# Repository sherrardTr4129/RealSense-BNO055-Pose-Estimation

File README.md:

# RealSense-BNO055-Pose-Estimation
This repository contains required software to construct a Pose of a vision target by fusing its x,y,z coordinates from the Intel RealSense depth camera, with its quaternion orientation from the BNO055 sensor.

## Demo Video
Have a look at the youtube video below to see the system in action!

## System Description
As mentioned, this system seeks to capture the position (x,y,z coordinates) of a vision target using an Intel RealSense depth camera, while capturing it's orientation as a quaternion using a BNO055 sensor. These two data streams are combined into a 6-DOF pose using an approximate time synchornization technique. This system has a multitude of uses in the problem domain of human-robot interaction. Some of these applications include the generation of end-effector goal poses for a "mimic-me" teleoperation robot arm, or potentially the generation of entire arm trajectories for a robot arm to follow. Please have a look at the high-level system block diagram below.

### Intel RealSense Position Capture
The Intel RealSense position capture sub-system attempts to locate the vision target in a given RGB frame, and then attempts to extract the vision target's approximate depth and X,Y coordinates in the camera's coordinate frame. From here, these values are scaled and shifted accordingly and re-published to the rest of the system as a PointStamped message. Have a look at this sub-system's block diagram and a physical representation of the system components below. 

### BNO055 Orientation Capture
The BNO055 orientation capture sub-system attempts to determine the orientation of the vision target as a quaternion, and then wirelessly transmit said quaternion back to a base-station MCU. The base-station MCU then sends the quaternion to a ROS node running on a local computer via a serial interface. This ROS node processes the quaternion components and publishes it as a quaternionStamped message to the rest of the system. All designs (mechanical, electrical and firmware) needed to construct the wirless orientation capture sub-system can be found [here](https://github.com/sherrardTr4129/Kinect-BNO055-Pose-Estimation/tree/main/orientation_capture_subsystem_hardware_and_firmware). The overall sub-system block diagram, functional flowchart diagram, as well as a visual representation of the system can be seen in the figures below.

## System Dependencies
The various dependencies of the system can be seen in the following sub-sections.

### Intel RealSense Dependencies
To run the Intel RealSense interfacing software generated in this project, make sure you have installed the [RealSense SDK 2](https://dev.intelrealsense.com/docs/compiling-librealsense-for-linux-ubuntu-guide) with python bindings.

### MCU Serial Interface Dependencies
The wirelss orientation data reciever MCU serial ROS driver depends on the pyserial library for serial connectiviy. This library can be installed by running the following command in a terminal:

```bash
sudo apt install python-serial
```

### Arduino Firmware Dependencies
Both the transmitter module and reciever module depend on the NRF24 library that can be obtained through the arduino IDE package manager. The transmitter module firmware also depends on the BNO055 sensor adafruit library and the adafruit unified sensor library (both can be obtained in the arduino IDE package manager. 

## Usage
This repository contains three distinct ROS packages that are described in more detail below. 

To launch both the Intel RealSense depth camera position capture node, BNO055 serial ROS driver, and sensor data stream fusion node, run the following in a terminal:
```bash
roslaunch kinect_bno_fusion kinect_bno_fusion_bringup.launch
```

Once these nodes are up and running successfully, you can launch the gazebo visualization tool by running the following in a terminal:
```bash
roslaunch gazebo_pose_example kinect_set_pose_demo.launch
```
This will launch a Gazebo instance, in which a cube will be instantiated that will have it's Pose set by the Pose generated from the sensor data fusion node that was launched in the last step.

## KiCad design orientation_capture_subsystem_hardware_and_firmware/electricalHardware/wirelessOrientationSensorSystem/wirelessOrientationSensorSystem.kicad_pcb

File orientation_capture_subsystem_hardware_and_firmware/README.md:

# Orientation Capture Sub-System Designs (Electrical and Mechanical) and Firmware
This directory contains the hardware designs (mechanical and electrical) and firmware needed to construct the wireless orientation capture system used for more robust motion capture.

# Overall System Specifications
The table below outlines some basic specifications for the overall orientation capture sub-system:

|                       Specification                       |                              Value                              |
|:---------------------------------------------------------:|:---------------------------------------------------------------:|
| Transmitter Range                                         | At least 5m (probably much more even at the NRF24_PA_LOW value) |
| Transmitter Sub-System Current Consumption (steady state) | ~50mA                                                           |
| Battery Life (Assuming 1Ah cell)                          | ~20 hours                                                       |
| Transmitter Input Voltage (4 AA battery cell recommended) | 5V - 6V                                                         |
| Overall System Data Frame Rate                            | ~30 FPS                                                         |

# Electrical Hardware Designs
For this project, a PCB was designed containing all required hardware to read data packets from the BNO055 sensor and transmit them wirelessly to a basestation, where they can be read in by the aforementioned ROS driver. The kiCAD project containng the schematic and board layout files can be found in the electricalHardware/wirelessOrientationSensorSystem directory in this repository. Please see below for a wiring diagram for both the base-station and wireless transmitter board and well as real pictures of each device. 

## Sensor Data Transmitter

Please note that this diagram depicts the wireless data tranmission module in its operational state. More connections are required to flash the firmware to the device. These connections and the firmware flashing process will be outlined later in this readme.

## Sensor Data Reciever 

# Firmware
The firmware flashing process for each of the board assemblies can be seen in each respective sub-section.

## Sensor Data Transmitter Firmware Flashing Procedure
As this board uses a unflashed ATMEGA328P processor, we must first flash the arduino bootloader to the device. The first step in this process is to wire an external arduino uno to the wireless data transmitter board in the configuration seen below. 

From here, upload the arduino as ISP sketch to the arduino uno found under File->Examples->ArduinoISP. Once this successfully uploads to the arduino uno, the bootloader can be flashed. The first step in the flashing process is to change the programmer under Tools->Programmer from "AVRISP mkll" to "Arduino As ISP". From here, click Tools->Burn Bootloader. If the process works as expected, a "bootloader flashed successfully" message will appear in the status window of the IDE

To flash the application level firmware onto the board, first disconnect the arduino uno from the wireless sensor transmitter board. From here, wire up the FTDI USB to TTL Serial converter to the wireless sensor transmitter as shown in the figure below.

From here, open the BNO005_Capture_and_Transmit.ino file in the Arduino IDE. Change the programmer back to "AVRISP mkll" from "Arduino As ISP". Make sure the correct serial port and board type (arduino uno) are selected under the tools menu. From here, click the upload button, and the source should compile and be uploaded to the MCU. 

## Sensor Data Reciever Firmware Flashing Procedure
The process for flashing the firmware for the reciever sub-system is the same as flashing any standard Arduino Uno. Just make sure you have all the NRF24 dependencies installed and compile and upload the firmware. 

# Mechanical Hardware Designs 
The mechanical hardware designs for both the vision target and the base station can be seen in the rendered images below. Note that both the these STL files are available in this repository.

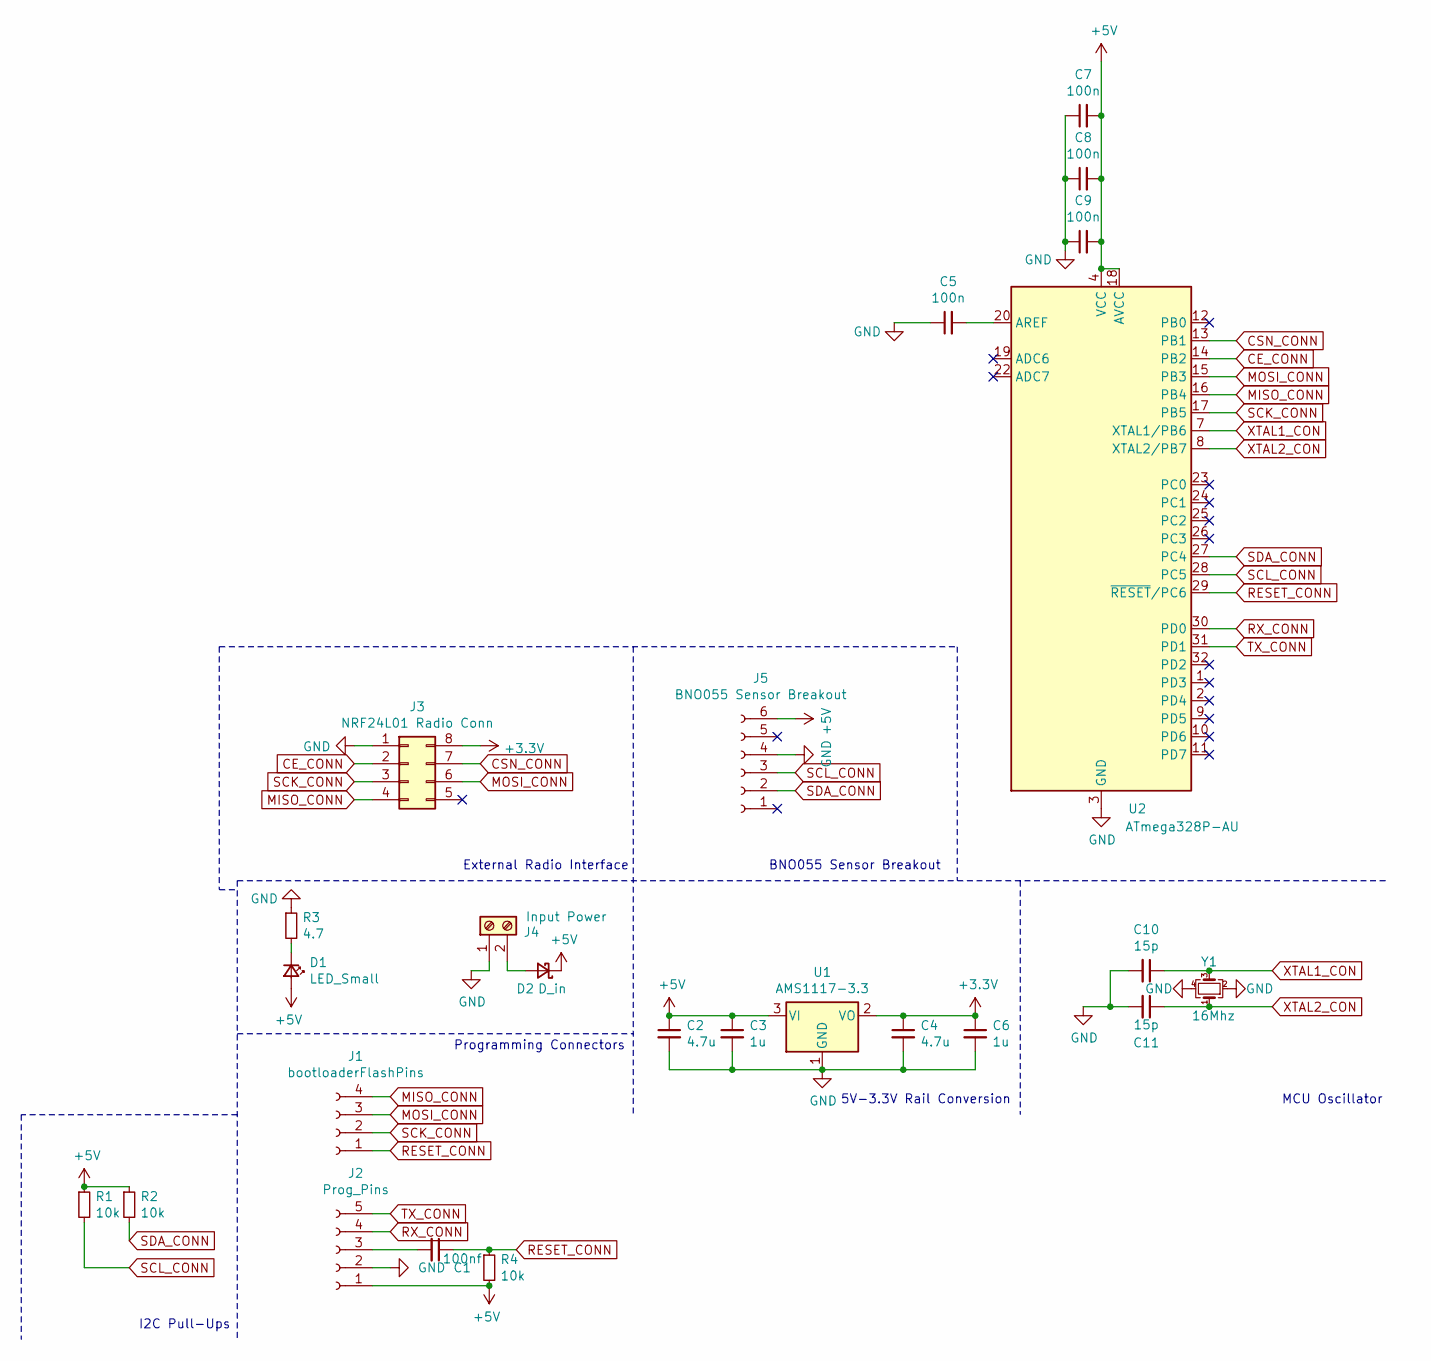
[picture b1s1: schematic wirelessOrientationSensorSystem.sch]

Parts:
C1: 100nf; C_0603_1608Metric; LCSC C14663
C2, C4: 4.7u; C_0805_2012Metric; LCSC C1779
C3, C6: 1u; C_0805_2012Metric; LCSC C28323
C5, C7, C8, C9: 100n; C_0603_1608Metric; LCSC C14663
C10, C11: 15p; C_0603_1608Metric; LCSC C1644
D1: LED_Small; LED_0805_2012Metric; LCSC C84256
D2: D_in; D_SOD-123; LCSC C8598
J1: bootloaderFlashPins; fourPinConn
J2: Prog_Pins; fivePinConn
J3: NRF24L01 Radio Conn; TwoByFourPins
J4: Input Power; 2-pinScrewTerm
J5: BNO055 Sensor Breakout; sixPinConn
R1, R2, R4: 10k; R_0603_1608Metric; LCSC C25804
R3: 4.7; R_0805_2012Metric; LCSC C17673
U1: AMS1117-3.3; SOT-223-3_TabPin2; LCSC C6186
U2: ATmega328P-AU; TQFP-32_7x7mm_P0.8mm; LCSC C14877
Y1: 16Mhz; Crystal_SMD_2520-4Pin_2.5x2.0mm; LCSC C284159

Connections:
+3V3: C4.1, C6.1, J3.8, U1.2 (VO)
+5V: C2.1, C3.1, C7.2, C8.2, C9.2, D1.2 (A), D2.1 (K), J2.1, J5.6, R1.1, R2.1, R4.2, U1.3 (VI), U2.4 (VCC), U2.6 (VCC), U2.18 (AVCC)
CE_CONN: J3.2, U2.14 (PB2)
CSN_CONN: J3.7, U2.13 (PB1)
GND: C2.2, C3.2, C4.2, C5.1, C6.2, C7.1, C8.1, C9.1, C10.2, C11.2, J2.2, J3.1, J4.1, J5.4, R3.1, U1.1 (GND), U2.3 (GND), U2.5 (GND), U2.21 (GND), Y1.2, Y1.4
MISO_CONN: J1.4, J3.4, U2.16 (PB4)
MOSI_CONN: J1.3, J3.6, U2.15 (PB3)
unnamed: C1.2, J2.3
unnamed: C5.2, U2.20 (AREF)
unnamed: D1.1 (K), R3.2
unnamed: D2.2 (A), J4.2
RESET_CONN: C1.1, J1.1, R4.1, U2.29 (~RESET~/PC6)
RX_CONN: J2.4, U2.30 (PD0)
SCK_CONN: J1.2, J3.3, U2.17 (PB5)
SCL_CONN: J5.3, R1.2, U2.28 (PC5)
SDA_CONN: J5.2, R2.2, U2.27 (PC4)
TX_CONN: J2.5, U2.31 (PD1)
XTAL1_CON: C10.1, U2.7 (XTAL1/PB6), Y1.3
XTAL2_CON: C11.1, U2.8 (XTAL2/PB7), Y1.1

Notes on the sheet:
MCU Oscillator
5V-3.3V Rail Conversion
Programming Connectors
External Radio Interface
I2C Pull-Ups
BNO055 Sensor Breakout

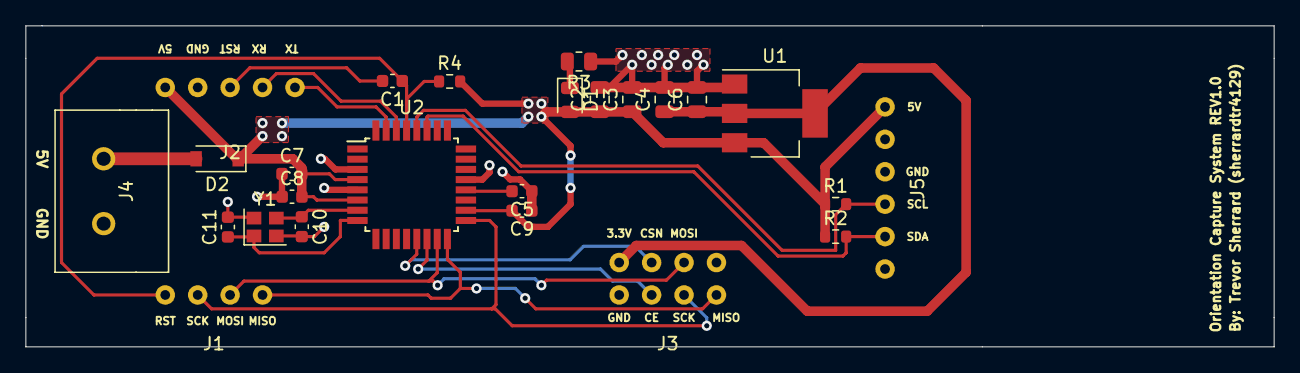
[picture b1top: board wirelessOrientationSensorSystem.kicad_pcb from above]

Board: 2 copper layers, 97.8 x 25.1 mm, 25 parts (0 on the bottom side), 19 nets.

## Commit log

2021-02-03 initial commit of BNO055 ROS driver
2021-02-07 initial commit of kinect vision processing node
2021-02-07 finished kinect point publisher
2021-02-07 update messages to have headers
2021-02-07 add node to demonstrate Pose control in gazebo
2021-02-07 WIP commit: add more comments
2021-02-08 add more comments
2021-02-08 Update README.md
    update readme
2021-02-08 add diagrams
2021-02-13 add comment
2021-02-13 add check to see if gazebo service is up
2021-02-13 move from quaternion processing to euler
2021-02-13 add scaling factors
2021-02-14 try to smooth out noise
2021-02-14 swap IMU axes
2021-02-20 add wireless orientation sensor kicad project
2021-02-20 add transmitter and reciever firmware
2021-02-20 add readme
2021-02-20 add check for nan values
2021-02-20 add link to orientation capture sub-system digital assets
2021-02-20 add more information to readme
2021-02-20 add two new documentation images
2021-02-20 resize images
2021-02-20 add two more images
2021-02-20 resize image
2021-02-21 add STL files
2021-02-21 cnange baud rate
2021-02-21 add gitignore
2021-02-27 WIP Commit
2021-04-02 another WIP commit
2021-04-03 change topic name for 3D point
2021-04-03 add scalers and offsets
2021-04-12 add image publishing stuff
2021-04-12 add moving average for all three axes back in
2021-05-03 add new images
2021-05-20 fix image issue
